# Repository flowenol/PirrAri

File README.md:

# PirrAri

A fully web controlled RC Ferrari model based on rPi and Arduino with camera support.

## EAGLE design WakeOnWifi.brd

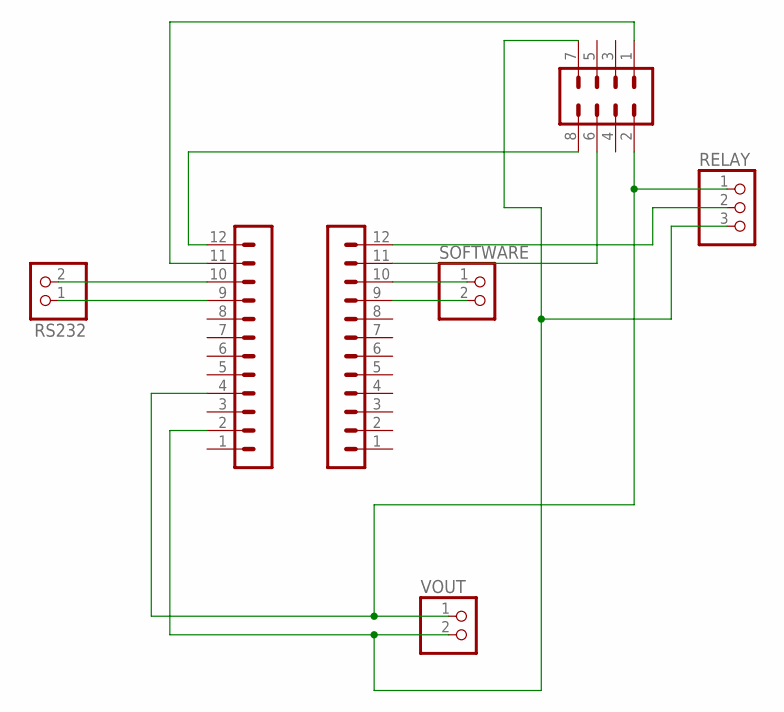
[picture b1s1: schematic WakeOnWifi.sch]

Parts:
ARDUINOLEFT: MA12-1
ARDUINORIGHT: MA12-1
RELAY: PINHD-1X3; 1X03
RS232: PINHD-1X2; 1X02
SOFTWARE: PINHD-1X2; 1X02
VOUT: PINHD-1X2; 1X02
WIFI: MA04-2

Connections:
unnamed: ARDUINOLEFT.2, RELAY.3, VOUT.2, WIFI.7
unnamed: ARDUINOLEFT.12, WIFI.8
unnamed: ARDUINOLEFT.11, WIFI.1
unnamed: ARDUINOLEFT.4, RELAY.1, VOUT.1, WIFI.2
unnamed: ARDUINORIGHT.11, WIFI.6
unnamed: ARDUINORIGHT.10, SOFTWARE.1
unnamed: ARDUINORIGHT.9, SOFTWARE.2
unnamed: ARDUINORIGHT.12, RELAY.2
unnamed: ARDUINOLEFT.10, RS232.2
unnamed: ARDUINOLEFT.9, RS232.1

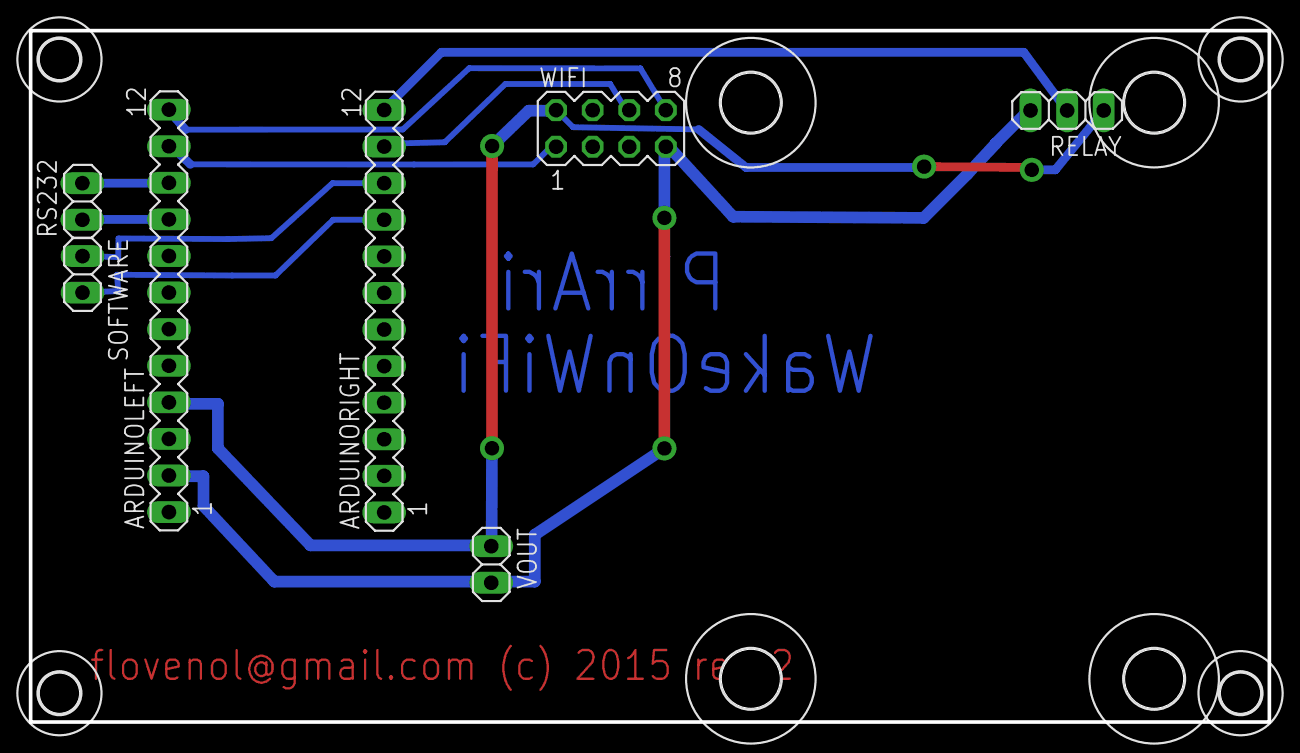
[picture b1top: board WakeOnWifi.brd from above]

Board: 2 copper layers, 86.0 x 48.0 mm, 15 parts (0 on the bottom side), 10 nets.

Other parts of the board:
U$1, U$2, U$3, U$4: 2,8
U$5, U$6, U$7, U$8: 4,1

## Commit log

2015-02-06 new features
    - motor readiness monitoring
    - power off for motor control and analog sensors
    - overall and motor current monitoring
2015-02-10 Power switch button
2015-02-10 Camera support
2015-02-12 camera port parameter, touch and mouse controls.
2015-02-12 description update.
2015-02-14 Wake on WiFi.
2015-02-15 Software Update signal.
2015-02-16 Camera, WakeOnWifi fixes
2015-02-17 Camera switch off fix.
2015-02-27 WakeOnWifi on Pro Micro, peripherals power default off
2015-05-10 Current sensor calibration
2015-05-18 further current calibration and GUI fixes
2015-05-25 WakeOnWifi board design
2015-06-15 WakeOnWifi board fixes
2015-07-11 signal level & software update script
2015-07-24 switch to Spring Boot.
2015-11-28 spring boot + various fixes
2015-11-28 controller code purification

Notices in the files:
WakeOnWifi.brd:
flovenol@gmail.com (c) 2015 rev 2
